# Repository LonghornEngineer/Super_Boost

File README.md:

***
###Super_Boost
***
**Dual footprint for the P8X32A-Q44 and P8X32A-M44 32-bit MCU.**

The Super Boost uses the LM2700 to boost to 5V to charge USB devices.

See [here for more information](http://longhornengineer.com/category/projects/hardware/super-boost/).

***
**License Information**

This project is under the [Creative Commons Attribution-ShareAlike 4.0 International License](LICENSE.md). These files are provided with no warranty and should be used at your own risk. 

***

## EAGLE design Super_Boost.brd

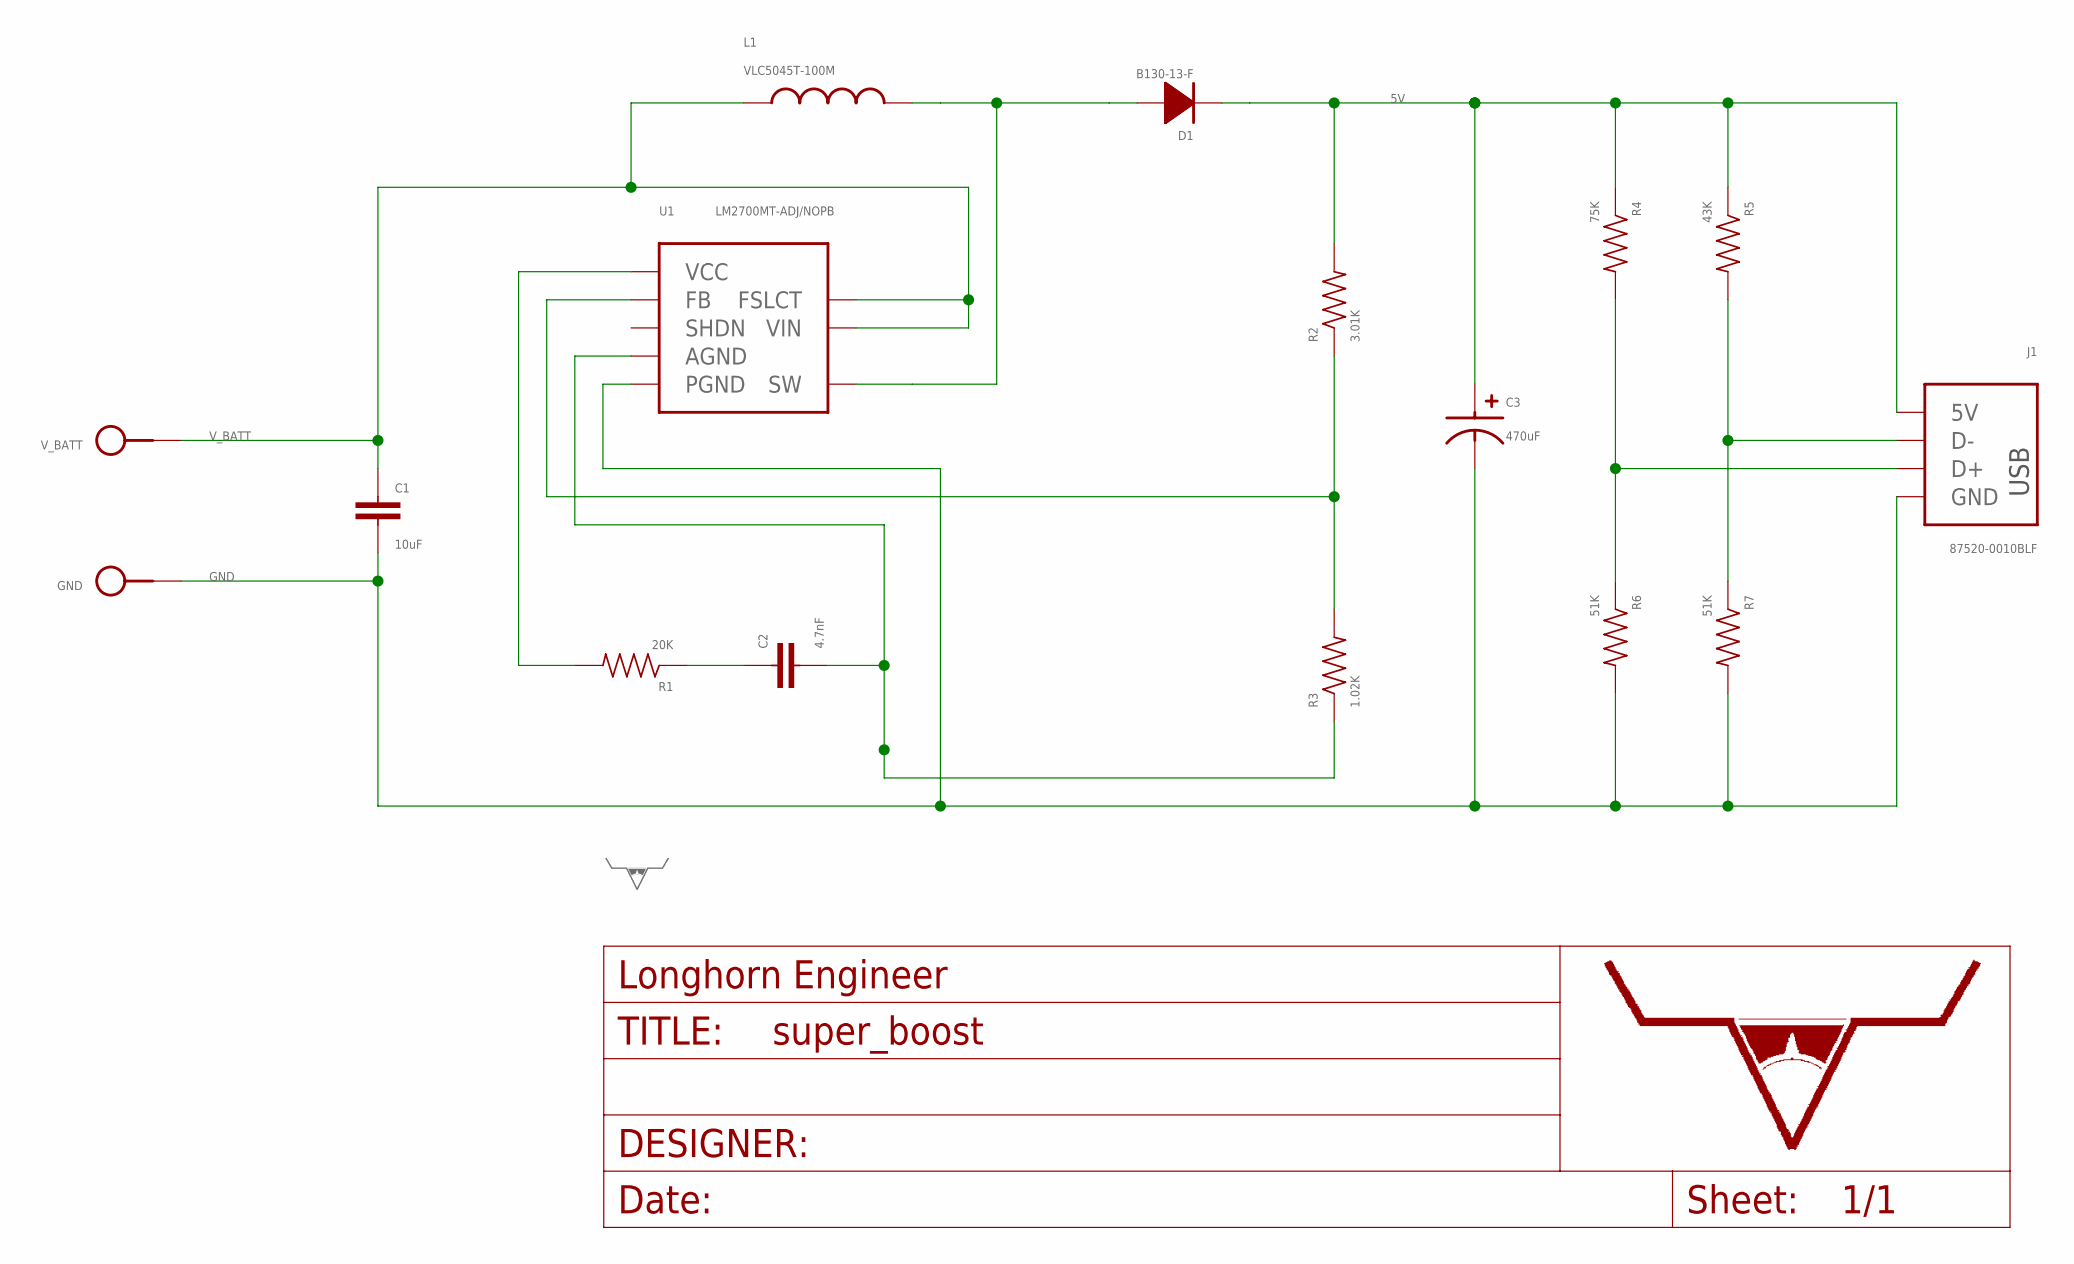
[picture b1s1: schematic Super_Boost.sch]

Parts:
C1: 10uF; 0603
C2: 4.7nF; 0805
C3: 470uF; 10MM_CAP_SMD
D1: B130-13-F
GND: TEST_POINT_SINGLEKEYSTONE_5115-5119; KEYSTONE_5115-5119
J1: 87520-0010BLF
L1: VLC5045T-100M; VLC5045
R1: 20K; 0603
R2: 3.01K; 0603
R3: 1.02K; 0603
R4: 75K; 0603
R5: 43K; 0603
R6, R7: 51K; 0603
U1: LM2700MT-ADJ/NOPB; TSSOP-14
U$1: LHE_LOGO
U$5: LHE_FRAME
V_BATT: TEST_POINT_SINGLEKEYSTONE_5115-5119; KEYSTONE_5115-5119

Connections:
5V: C3.POS, D1.CATHODE, J1.5V, R2.2, R4.1, R5.1
AGND: C2.2, R3.1, U1.4 (AGND)
FB: R2.1, R3.2, U1.2 (FB)
GND: C1.2, C3.NEG, GND.P$1, J1.GND, J1.SHLD0 (GND), J1.SHLD1 (GND), R6.2, R7.2, U1.5 (PGND), U1.6 (PGND), U1.7 (PGND)
unnamed: C2.1, R1.1
unnamed: J1.D+, R4.2, R6.1
unnamed: J1.D-, R5.2, R7.1
SW: D1.ANODE, L1.P$2, U1.8 (SW), U1.9 (SW), U1.10 (SW)
VC: R1.2, U1.1 (VCC)
V_BATT: C1.1, L1.P$1, U1.12 (VIN), U1.13 (FSLCT), V_BATT.P$1

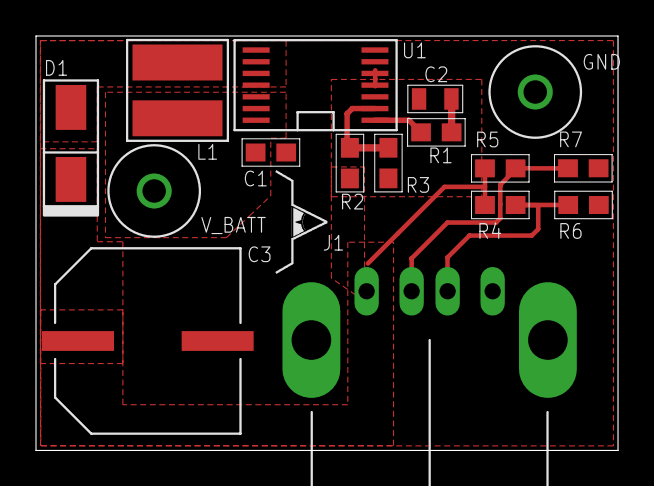
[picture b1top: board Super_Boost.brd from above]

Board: 2 copper layers, 32.3 x 23.0 mm, 18 parts (1 on the bottom side), 10 nets.

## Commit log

2014-01-09 First Push. REV 2.
2014-04-09 Update to CC-BY-SA License.
2016-08-23 updating readme.

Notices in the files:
parts and their libraries:
PP_Aesthetics: (c) 2013 Longhorn Engineer
